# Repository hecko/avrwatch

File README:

plne funkcna a otestovana na ATMega8L - PDIP verzia

  xtal (32kHz) musi byt zapojeny s externymi kondenzatormi (pozri errata v datasheete atmega8l) - pouzite 22pF (oznacenie 22) (na kazdej nozicke prepojene s GND)
  vsetky GND prepojene
  vsetky VCC prepojene
  AREF prepojeny cez 100n (oznacenie 104) kondenzator na GND
  7 segment display SA36-11GWA cez cca 100 Ohm odpory (spolocna anoda)
  tlacitla su medi INT pinmi a GND s 10K resistormi na pinoch do VCC
  napajane cez CR2032, alebo 2xAA 

programovanie je testovane na programatore usbtiny

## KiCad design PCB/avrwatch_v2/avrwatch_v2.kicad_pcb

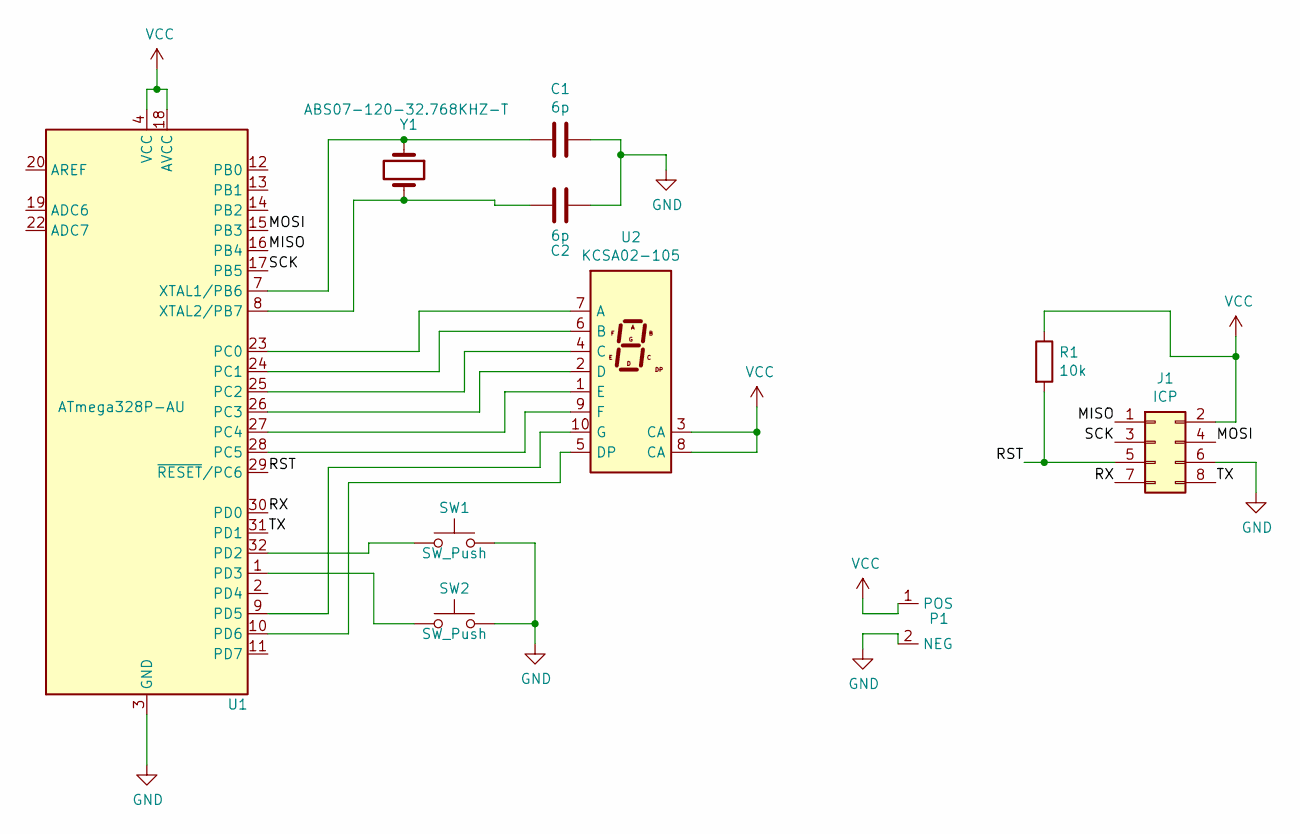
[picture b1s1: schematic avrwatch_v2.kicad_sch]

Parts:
C1, C2: 6p; C_0603_1608Metric
J1: ICP; PinHeader_2x04_P2.54mm_Vertical
P1: CR2032-120591
R1: 10k; R_0603_1608Metric
SW1, SW2: SW_Push; SW_PUSH_6mm_H9.5mm_center
U1: ATmega328P-AU; TQFP-32_7x7mm_P0.8mm
U2: KCSA02-105; KCSC02-105
Y1: ABS07-120-32.768KHZ-T; Crystal_SMD_3215-2Pin_3.2x1.5mm; FARNELL 2467864

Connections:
/MISO: J1.1, U1.16 (PB4)
/MOSI: J1.4, U1.15 (PB3)
/RST: J1.5, R1.2, U1.29 (~RESET/PC6)
/RX: J1.7, U1.30 (PD0)
/SCK: J1.3, U1.17 (PB5)
/TX: J1.8, U1.31 (PD1)
GND: C1.1, C2.1, J1.6, P1.2 (NEG), SW1.2, SW2.2, U1.3 (GND), U1.5 (GND), U1.21 (GND)
unnamed: U1.23 (PC0), U2.7 (A)
unnamed: U1.24 (PC1), U2.6 (B)
unnamed: U1.25 (PC2), U2.4 (C)
unnamed: U1.26 (PC3), U2.2 (D)
unnamed: U1.27 (PC4), U2.1 (E)
unnamed: U1.28 (PC5), U2.9 (F)
unnamed: SW1.1, U1.32 (PD2)
unnamed: SW2.1, U1.1 (PD3)
unnamed: U1.9 (PD5), U2.10 (G)
unnamed: U1.10 (PD6), U2.5 (DP)
unnamed: C1.2, U1.7 (XTAL1/PB6), Y1.1
unnamed: C2.2, U1.8 (XTAL2/PB7), Y1.2
VCC: J1.2, P1.1 (POS), R1.1, U1.4 (VCC), U1.6 (VCC), U1.18 (AVCC), U2.3 (CA), U2.8 (CA)

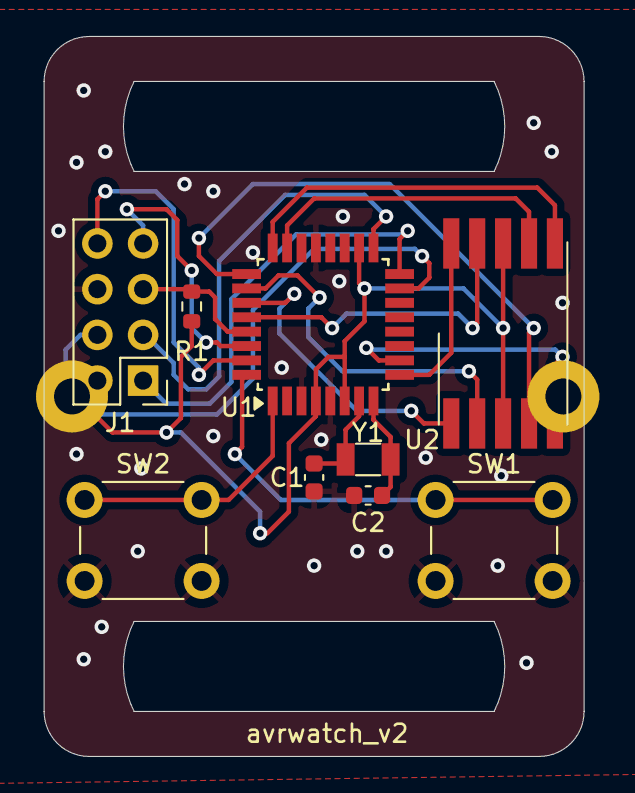
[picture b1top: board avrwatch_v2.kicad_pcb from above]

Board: 2 copper layers, 30.0 x 40.0 mm, 10 parts (1 on the bottom side), 20 nets.

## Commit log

2012-10-22 moving from google code to github
2012-10-22 programator
2012-10-22 added wiring diagram
2013-03-14 Update rtc.c
    opravene gramaticke chyby
2013-03-14 Update TODO
2013-03-14 [code] renamed readme file to show picture on github
2013-03-14 [doc] added atmega diagram into docs
2021-12-16 simplest possible design with atmega328p
2024-09-25 finishing the pcb
2024-09-25 needs battery fixing
